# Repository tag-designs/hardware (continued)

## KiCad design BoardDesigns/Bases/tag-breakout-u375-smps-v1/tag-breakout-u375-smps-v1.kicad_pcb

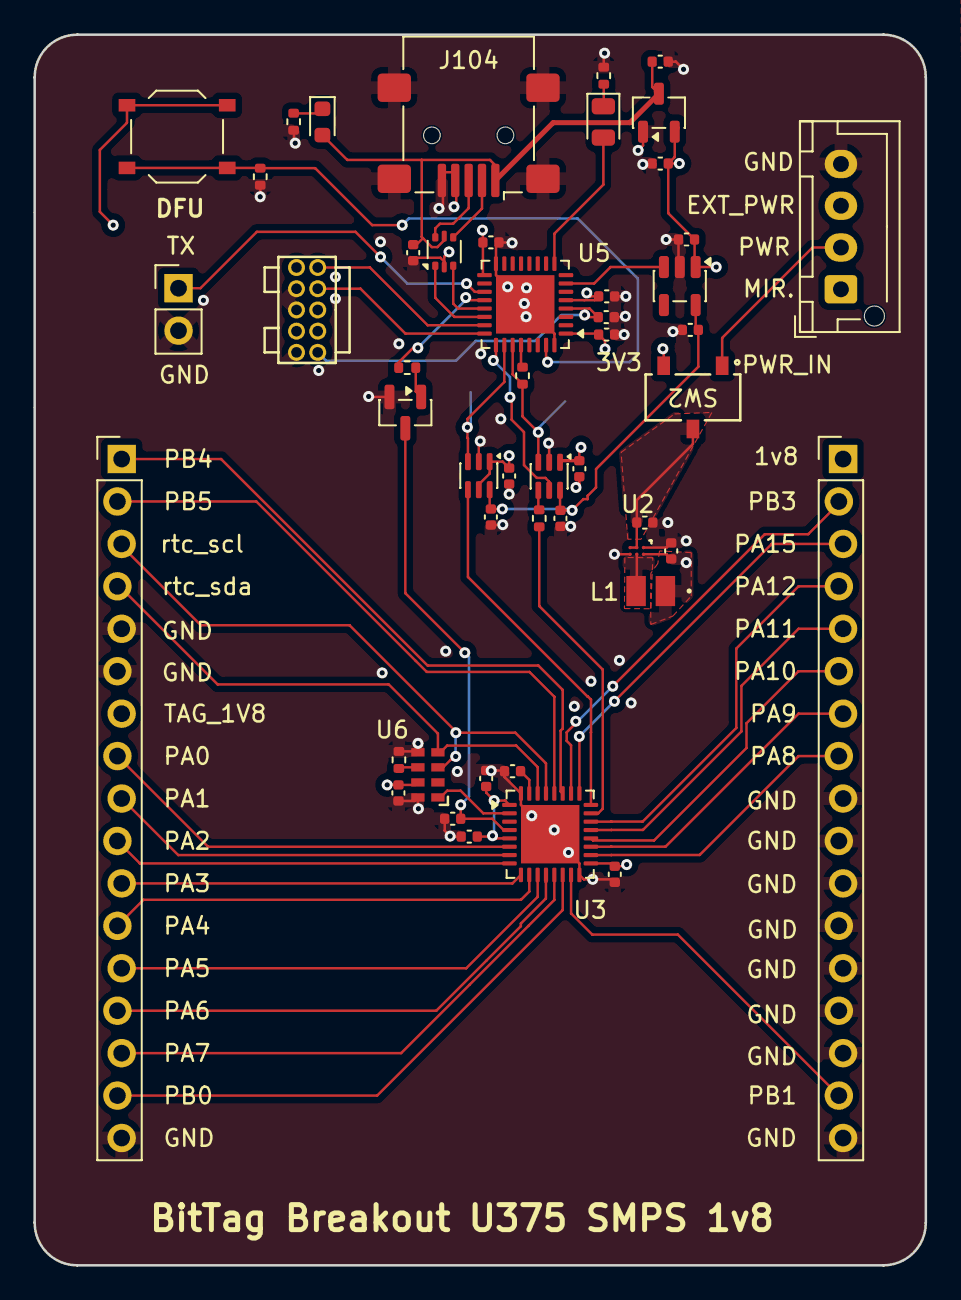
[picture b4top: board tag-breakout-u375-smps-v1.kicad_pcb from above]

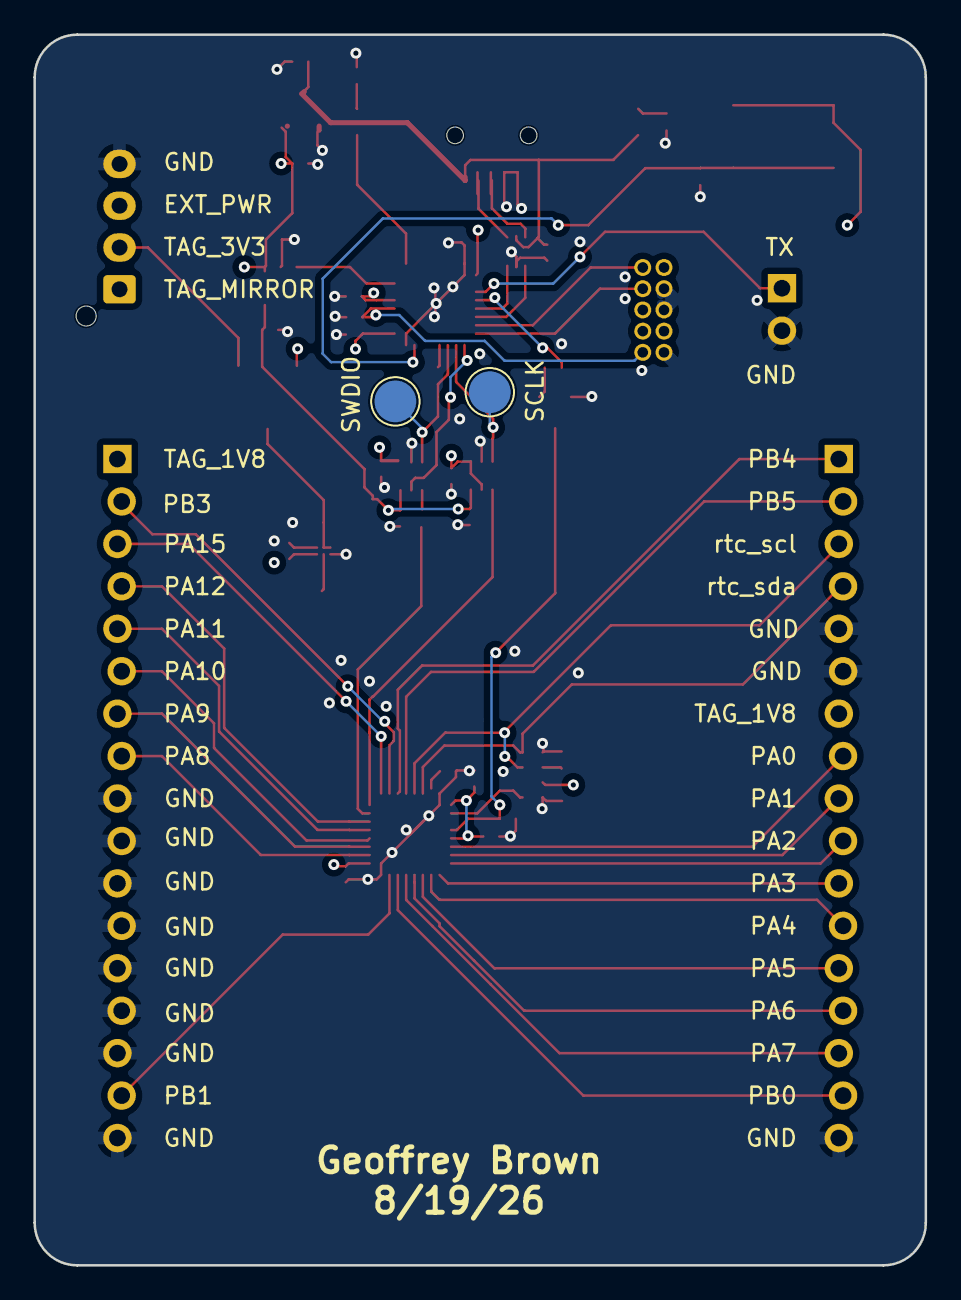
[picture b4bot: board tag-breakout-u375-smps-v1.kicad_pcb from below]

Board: 4 copper layers, 53.3 x 73.7 mm, 51 parts (2 on the bottom side), 55 nets.

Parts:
C1, C12, C104, C105: 1uF; C_0402_1005Metric
C2, C3, C5, C6, C7, C9, C11, C101, C102, C103, C107, C109, C110, C111: 0.1uF; C_0402_1005Metric
C4: 10uf; C_0402_1005Metric
C8, C10: 4.7uf; C_0402_1005Metric
D1: LED; LED_0805_2012Metric
D105: LED; LED_0603_1608Metric
J1: Conn_01x04_Female; JST_XH_B04B-XH-AM_1x04_P2.50mm_Vertical
J2: Conn_01x02_Male; PinHeader_1x02_P2.54mm_Vertical
J3, J4: Conn_01x17; PinHeader_1x17_P2.54mm_Vertical_Staggered
J102: Conn_02x05_Odd_Even; FTSH-105-01-F-D-K
J104: USB_B_Mini; USB_Mini-B_Lumberg_2486_01_Horizontal
L1: 2.2uH; IND_DFE2016_MUR
Q1: Q_NPN_BEC; SOT-23
R1, R2, R106: 100; R_0402_1005Metric
R3, R105: 12K; R_0402_1005Metric
R104: 2.2K; R_0402_1005Metric
R107: 200; R_0402_1005Metric
SW2: SW_SPDT; CJS-1200B_NDC
TP1, TP2: TestPoint; TestPoint_Pad_D2.5mm
U1: XC6206; SOT-23-3
U2: TPS62840YBGR; DSBGA6_1P4XP9_TEX
U3: stm32U375; UFQFPN-32-1EP_5x5mm_P0.5mm_EP3.5x3.5mm
U4: USBLC6-2P6; SOT-666
U5: STM32L432KBU6; UFQFPN-32-1EP_5x5mm_P0.5mm_EP3.5x3.5mm
U6: RV-3028-C7; RV-8803-C7
U7, U8: SN74LVC1T45DCK; SOT-363_SC-70-6
U10: AP2112K-1.8; SOT-23-5
U105: Tactile Switch; SW_SPST_TS_1187

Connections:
+1V8: C103.1, C105.1, C109.1, U7.6 (VCCB), U8.6 (VCCB), U10.5 (VOUT)
+3V3: C2.1, C11.1, C12.1, C104.1, C107.1, C110.1, C111.1, J102.1, SW2.3 (C), U1.2 (VO), U5.1 (VDD), U5.5 (VDDA/VREF+), U5.17 (VDD), U7.1 (VCCA), U7.5 (DIR), U8.1 (VCCA), U10.1 (VIN), U105.2 (B)
/DM: J104.2 (D-), U4.4 (I/O2)
/DP: J104.3 (D+), U4.6 (I/O1)
/LED_GREEN: D1.2 (A), U5.9 (PA3)
/NRST: C101.1, J102.10, U5.4 (~NRST)
/SCLK: J102.4, U5.24 (PA14)
/SWDIO: J102.2, U5.23 (PA13)
/UART_TX: J2.1, U5.19 (PA9)
/USB_DM: U4.3 (I/O2), U5.21 (PA11)
/USB_DP: U4.1 (I/O1), U5.22 (PA12)
/boot0: R105.2, U5.31 (BOOT0), U105.1 (A)
/en1.8v: U5.7 (PA1), U10.3 (EN)
/stm32/NRST: C5.1, Q1.3 (C), U3.4 (~NRST)
/stm32/PA0: J3.8, U3.6 (PA0)
/stm32/PA1: J3.9, U3.7 (PA1)
/stm32/PA2: J3.10, U3.8 (PA2)
/stm32/PA3: J3.11, U3.9 (PA3)
/stm32/PA4: J3.12, U3.10 (PA4)
/stm32/PA5: J3.13, U3.11 (PA5)
/stm32/PA6: J3.14, U3.12 (PA6)
/stm32/PA7: J3.15, U3.13 (PA7)
/stm32/PA8: J4.8, U3.18 (PA8)
/stm32/PA9: J4.7, U3.19 (PA9)
/stm32/PA10: J4.6, U3.20 (PA10)
/stm32/PA11: J4.5, U3.21 (PA11)
/stm32/PA12: J4.4, U3.22 (PA12)
/stm32/PA15: J4.3, U3.25 (PA15)
/stm32/PB0: J3.16, U3.14 (PB0)
/stm32/PB1: J4.16, U3.15 (PB1)
/stm32/PB3: J4.2, U3.26 (PB3)
/stm32/PB4: J3.1, U3.27 (PB4)
/stm32/PB5: J3.2, U3.28 (PB5)
/stm32/VBACK: R3.2, U6.6 (VBACK)
/stm32/clkout: U3.2 (PC14), U6.1 (CLKOUT)
/stm32/rtc_scl: J3.3, U3.29 (PB6), U6.3 (SCL)
/stm32/rtc_sda: J3.4, U3.30 (BOOT0-PB7), U6.4 (SDA)
GND: C1.2, C2.2, C3.2, C4.2, C5.2, C6.2, C7.2, C8.2, C9.2, C10.2, C11.2, C12.2, C101.2, C102.2, C103.2, C104.2, C105.2, C107.2, C109.2, C110.2, C111.2, J1.4, J2.2, J3.5, J3.6, J3.17, J4.9, J4.10, J4.11, J4.12, J4.13, J4.14, J4.15, J4.17, J102.3, J102.5, J102.9, J104.4 (ID), J104.5 (GND), J104.SH (Shield), Q1.2 (E), R1.2, R3.1, R105.1, R107.2, U1.1 (GND), U2.A1 (GND), U2.C2 (VSET), U3.16 (VSS), U3.32 (VSS), U3.33 (GND), U4.2 (GND), U5.16 (VSS), U5.32 (VSS), U5.33 (GND), U6.5 (GND), U6.8 (EVI), U7.2 (GND), U8.2 (GND), U10.2 (GND)
unnamed: D1.1 (K), R1.1
unnamed: D105.1 (K), R107.1
unnamed: L1.2, U2.B2 (SW)
unnamed: C8.1, U3.31 (VCAP)
unnamed: R104.1, U5.20 (PA10)
unnamed: U5.25 (PA15), U8.5 (DIR)
unnamed: TP2.1 (1_1), U5.26 (PB3), U7.3 (A)
unnamed: R2.2, TP1.1 (1_1), U5.27 (PB4), U8.3 (A)
unnamed: R2.1, U5.28 (PB5)
unnamed: R106.1, U8.4 (B)
PWR_IN: J1.2, SW2.1 (A)
TAG_1V8: C3.1, C4.1, C6.1, C7.1, C9.1, J3.7, J4.1, L1.1, U2.A2 (VOS), U3.1 (VDD), U3.5 (VDDA/VREF+), U3.17 (VDD), U6.7 (VDD)
TAG_3V3: C10.1, SW2.2 (B), U2.B1 (VIN), U2.C1 (EN)
TAG_RESET: Q1.1 (B), R104.2
TAG_SCK: U3.24 (PA14), U7.4 (B)
TAG_SWDIO: R106.2, U3.23 (PA13)
VUSB: C1.1, C102.1, D105.2 (A), J104.1 (VBUS), U1.3 (VI), U4.5 (VBUS)

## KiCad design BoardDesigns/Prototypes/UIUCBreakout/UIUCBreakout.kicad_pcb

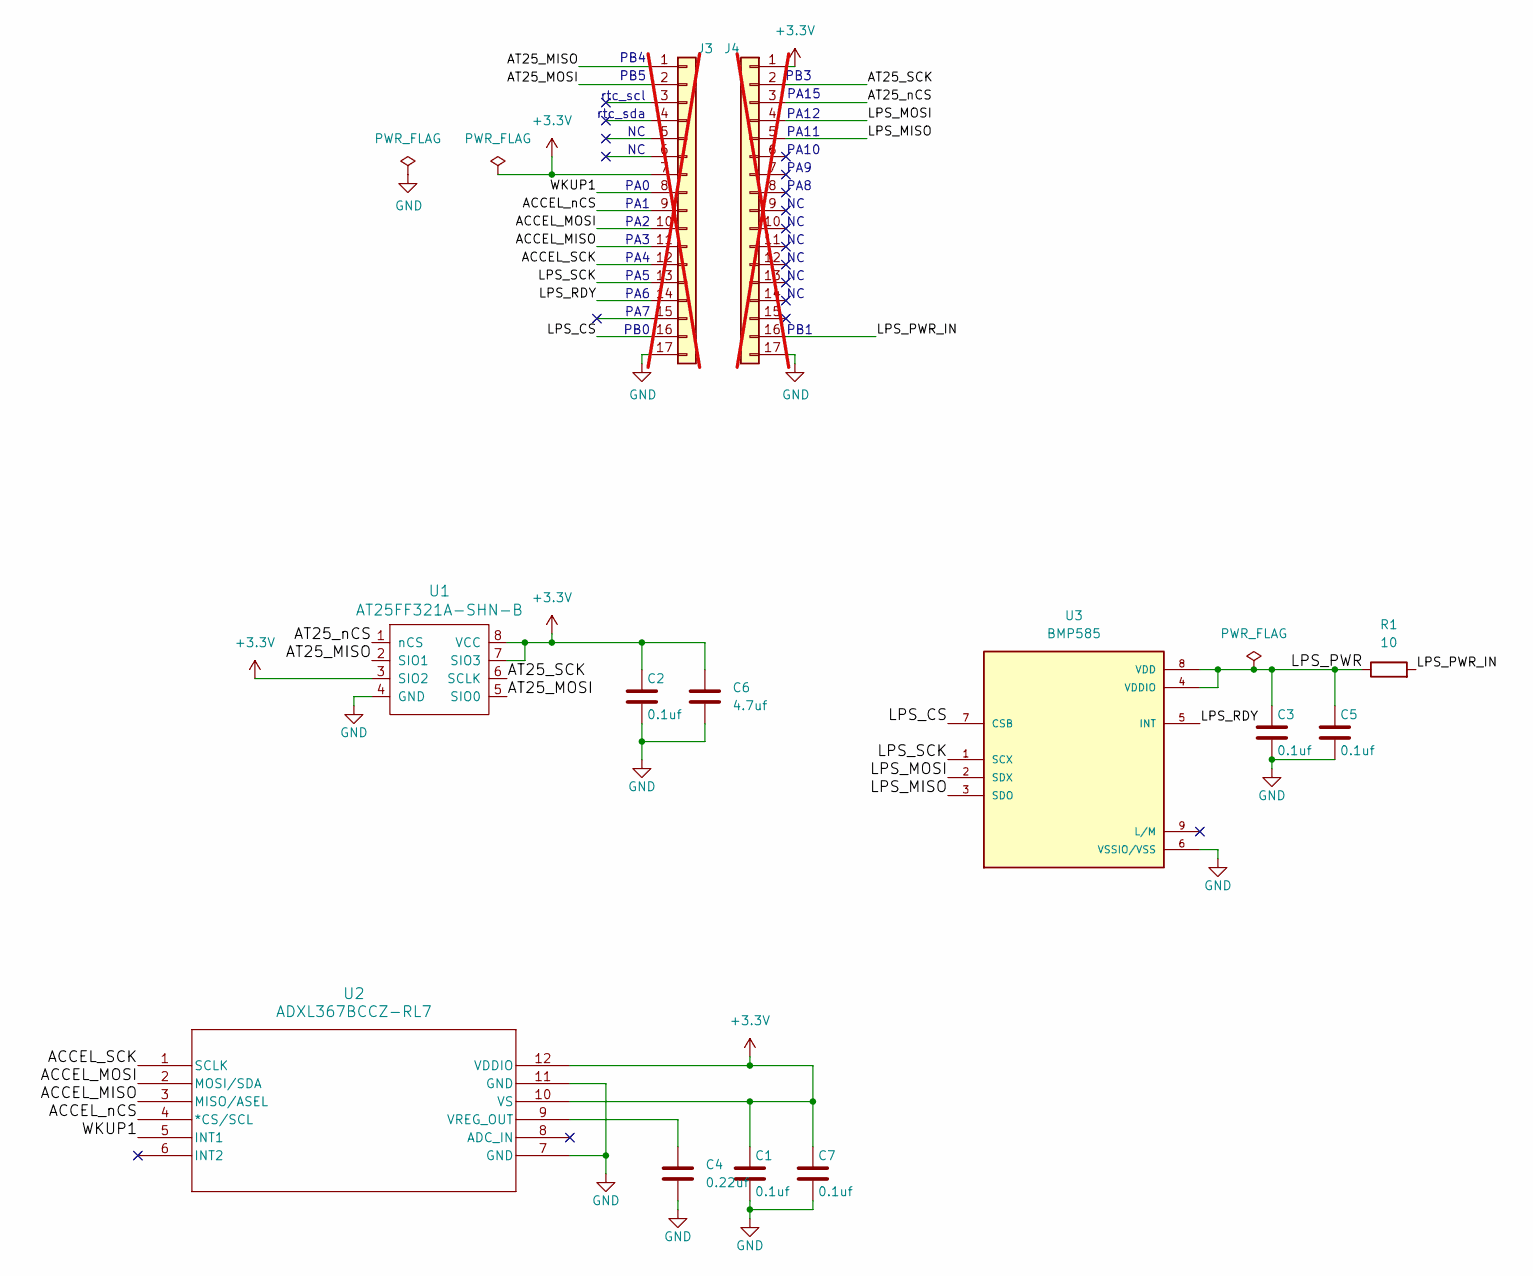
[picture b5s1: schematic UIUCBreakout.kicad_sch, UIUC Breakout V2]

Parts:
C1, C2, C3, C5, C7: 0.1uf; C_0603_1608Metric; MPN CC0603KRX7R9BB104; LCSC C14663
C4: 0.22uf; C_0603_1608Metric; MPN CL10B224KA8NNNC; LCSC C21120
C6: 4.7uf; C_0603_1608Metric; MPN CL10A475KO8NNNC; LCSC C19666
J3, J4: Conn_01x17; PinHeader_1x17_P2.54mm_Vertical_Staggered; not fitted
R1: 10; R_0603_1608Metric; MPN 0603WAF100JT5E; LCSC C22859
U1: AT25FF321A-SHN-B; SOIC-8_5.3x6.2mm_P1.27mm; MPN AT25FF321A-SHN-B; LCSC C5591126
U2: ADXL367BCCZ-RL7; CC-12-4_ADI; MPN ADXL367BCCZ-RL7; LCSC C17643415
U3: BMP585; LGA9_BMP585_BOS; PARTREV 1.2; LCSC C18184976

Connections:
+3.3V: C1.1, C2.1, C6.1, C7.1, J3.7, J4.1, U1.3 (SIO2), U1.7 (SIO3), U1.8 (VCC), U2.10 (VS), U2.12 (VDDIO)
/ACCEL_MISO: J3.11, U2.3 (MISO/ASEL)
/ACCEL_MOSI: J3.10, U2.2 (MOSI/SDA)
/ACCEL_SCK: J3.12, U2.1 (SCLK)
/ACCEL_nCS: J3.9, U2.4 (*CS/SCL)
/AT25_MISO: J3.1, U1.2 (SIO1)
/AT25_MOSI: J3.2, U1.5 (SIO0)
/AT25_SCK: J4.2, U1.6 (SCLK)
/AT25_nCS: J4.3, U1.1 (nCS)
/LPS_CS: J3.16, U3.7 (CSB)
/LPS_MISO: J4.5, U3.3 (SDO)
/LPS_MOSI: J4.4, U3.2 (SDX)
/LPS_PWR: C3.1, C5.1, R1.1, U3.4 (VDDIO), U3.8 (VDD)
/LPS_PWR_IN: J4.16, R1.2
/LPS_RDY: J3.14, U3.5 (INT)
/LPS_SCK: J3.13, U3.1 (SCX)
/WKUP1: J3.8, U2.5 (INT1)
GND: C1.2, C2.2, C3.2, C4.2, C5.2, C6.2, C7.2, J3.17, J4.17, U1.4 (GND), U2.7 (GND), U2.11 (GND), U3.6 (VSSIO/VSS)
unnamed: C4.1, U2.9 (VREG_OUT)

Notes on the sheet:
PA1
PA9
PA2
PA0
PA8
PA7
PA15
PA5
PA4
PB3
PA6
PA3
PB4
PA12
PB0
PB5
PA10
rtc_sda
PA11
PB1
rtc_scl

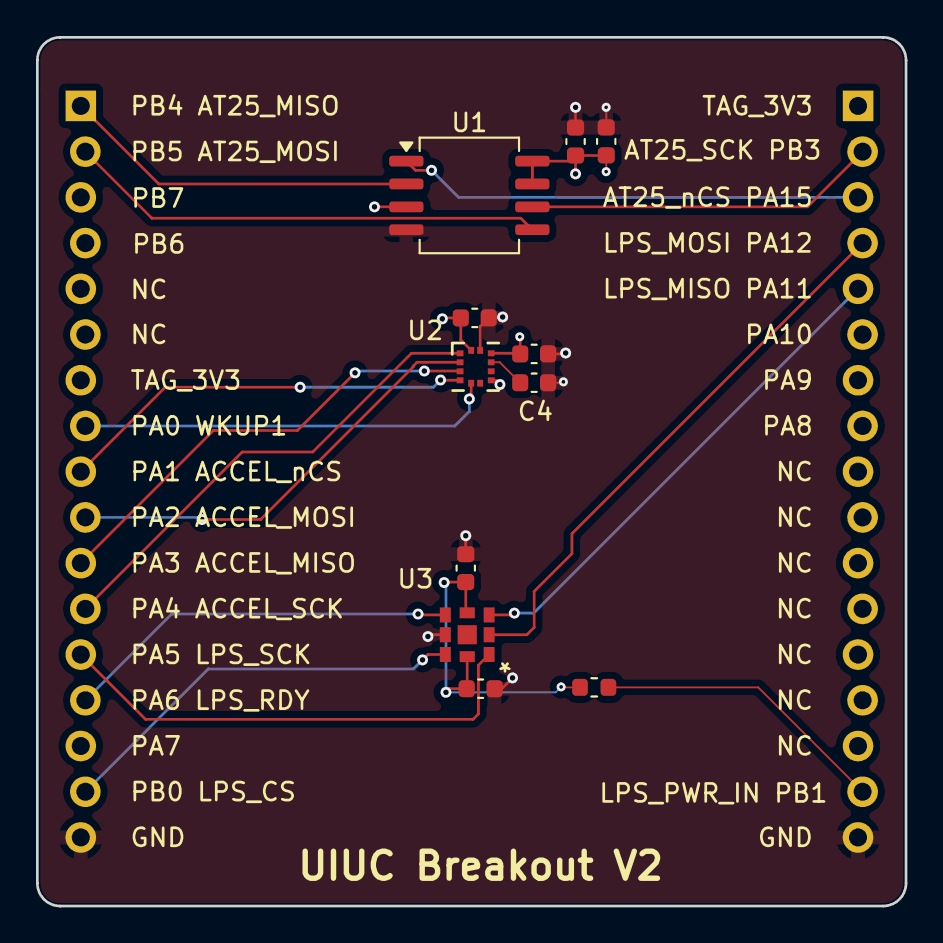
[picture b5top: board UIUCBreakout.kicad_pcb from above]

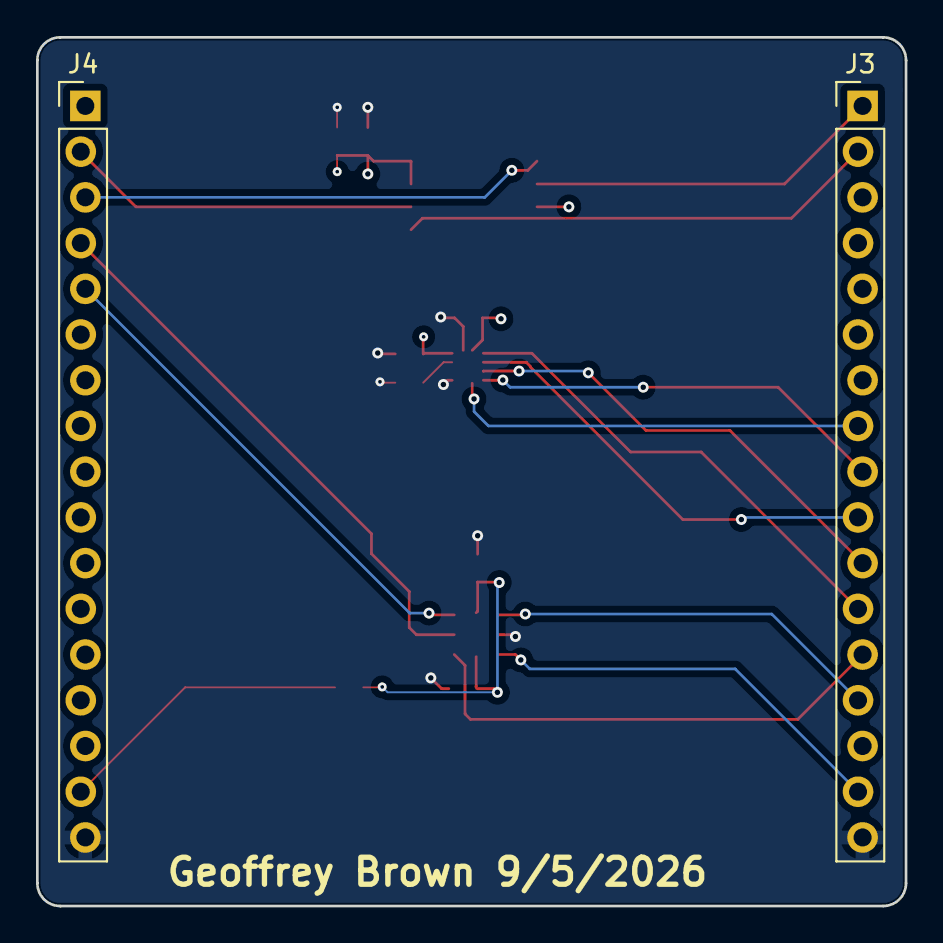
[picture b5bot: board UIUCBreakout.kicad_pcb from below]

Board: 4 copper layers, 48.3 x 48.3 mm, 13 parts (2 on the bottom side), 19 nets.

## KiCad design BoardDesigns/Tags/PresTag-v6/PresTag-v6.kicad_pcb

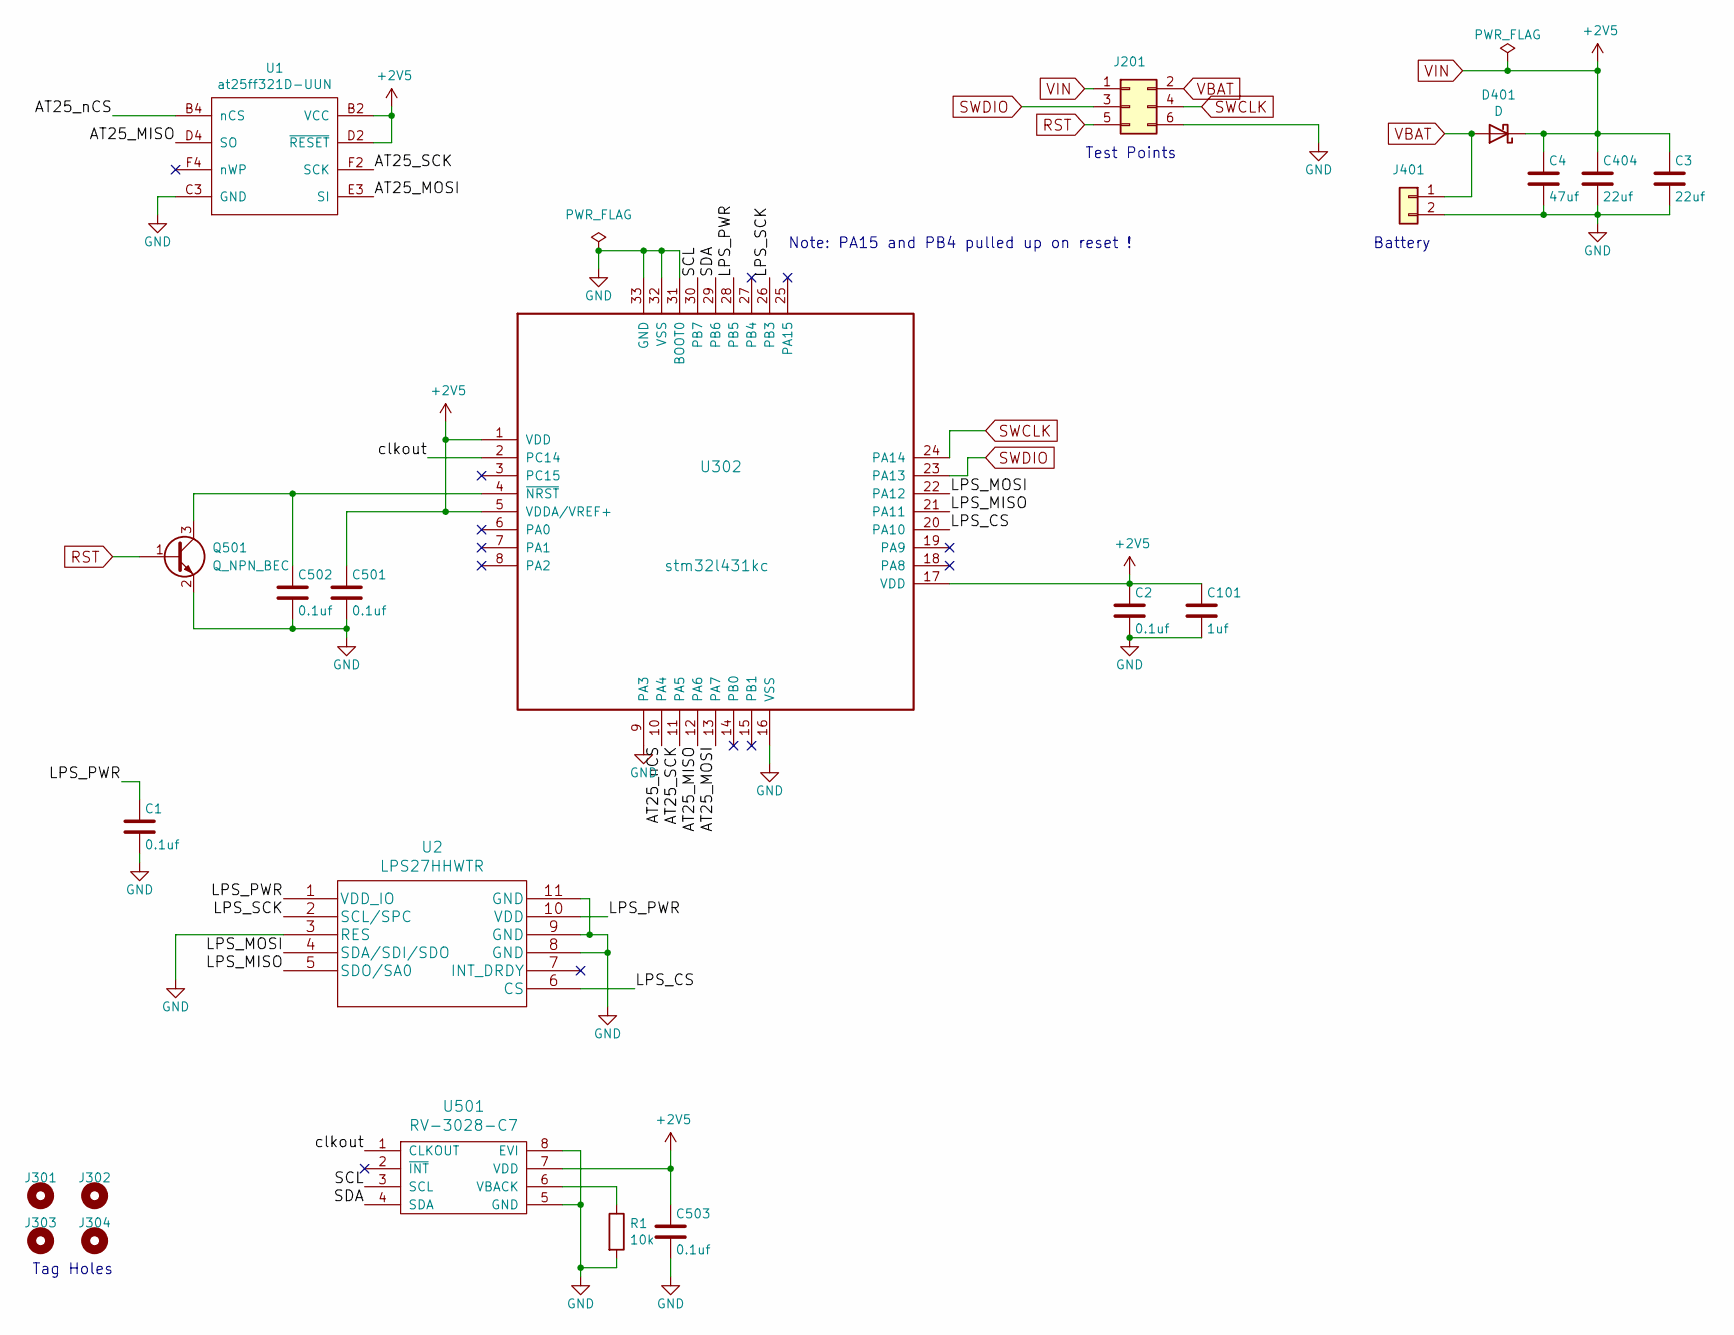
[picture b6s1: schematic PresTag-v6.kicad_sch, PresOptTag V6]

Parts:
C1, C2, C501, C502, C503: 0.1uf; C_0201_0603Metric; MPN GRM033C81E104KE14D
C3, C404: 22uf; C_0402_1005Metric; MPN 04026D226MAT2A
C4: 47uf; C_0603_1608Metric; MPN 06036D476MAT2A
C101: 1uf; C_0201_0603Metric; MPN GRM033R60J105MEA2D
D401: D; D_0402_1005Metric; MPN CDBQC0130L-HF
J201: CONN_02X04; tagpoints6
J301, J302, J303, J304: Conn_01x01; taghole1.1mm
J401: CONN_01X02; MS621
Q501: Q_NPN_BEC; SOT-883; MPN BC847AMB,315
R1: 10k; R_0201_0603Metric; MPN RC0201FR-0710KL
U1: at25ff321D-UUN; adesto_wlcsp12; MPN AT25FF321A-UUN-T (Mouser)
U2: LPS27HHWTR; MPN LPS27HHTWTR
U302: stm32l431kc; QFN-32-1EP_5x5mm_P0.5mm_EP3.45x3.45mm; MPN STM32L431KCU6
U501: RV-3028-C7; RV-8803-C7; MPN RV-3028-C7 32.768KHZ 1PPM-TA-QC

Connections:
/AT25_MISO: U1.D4 (SO), U302.12 (PA6)
/AT25_MOSI: U1.E3 (SI), U302.13 (PA7)
/AT25_SCK: U1.F2 (SCK), U302.11 (PA5)
/AT25_nCS: U1.B4 (nCS), U302.10 (PA4)
/LPS_CS: U2.6 (CS), U302.20 (PA10)
/LPS_MISO: U2.5 (SDO/SA0), U302.21 (PA11)
/LPS_MOSI: U2.4 (SDA/SDI/SDO), U302.22 (PA12)
/LPS_PWR: C1.1, U2.1 (VDD_IO), U2.10 (VDD), U302.28 (PB5)
/LPS_SCK: U2.2 (SCL/SPC), U302.26 (PB3)
/SCL: U302.30 (PB7), U501.3 (SCL)
/SDA: U302.29 (PB6), U501.4 (SDA)
/clkout: U302.2 (PC14), U501.1 (CLKOUT)
GND: C1.2, C2.2, C3.2, C4.2, C101.2, C404.2, C501.2, C502.2, C503.2, J201.6, J401.2, Q501.2 (E), R1.2, U1.C3 (GND), U2.3 (RES), U2.8 (GND), U2.9 (GND), U2.11 (GND), U302.9 (PA3), U302.16 (VSS), U302.31 (BOOT0), U302.32 (VSS), U302.33 (GND), U501.5 (GND), U501.8 (EVI)
unnamed: C502.1, Q501.3 (C), U302.4 (~NRST)
unnamed: R1.1, U501.6 (VBACK)
RST: J201.5, Q501.1 (B)
SWCLK: J201.4, U302.24 (PA14)
SWDIO: J201.3, U302.23 (PA13)
VBAT: D401.2 (A), J201.2, J401.1
VIN: C2.1, C3.1, C4.1, C101.1, C404.1, C501.1, C503.1, D401.1 (K), J201.1, U1.B2 (VCC), U1.D2 (~RESET), U302.1 (VDD), U302.5 (VDDA/VREF+), U302.17 (VDD), U501.7 (VDD)

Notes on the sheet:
Battery
Note: PA15 and PB4 pulled up on reset !
Tag Holes
Test Points

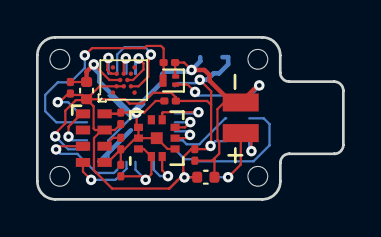
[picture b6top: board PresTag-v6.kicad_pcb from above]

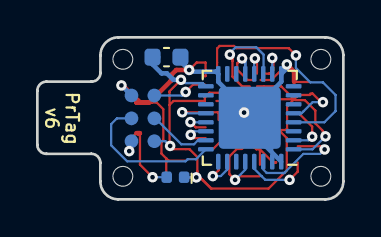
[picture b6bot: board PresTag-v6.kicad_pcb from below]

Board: 2 copper layers, 17.0 x 9.0 mm, 22 parts (4 on the bottom side), 20 nets.

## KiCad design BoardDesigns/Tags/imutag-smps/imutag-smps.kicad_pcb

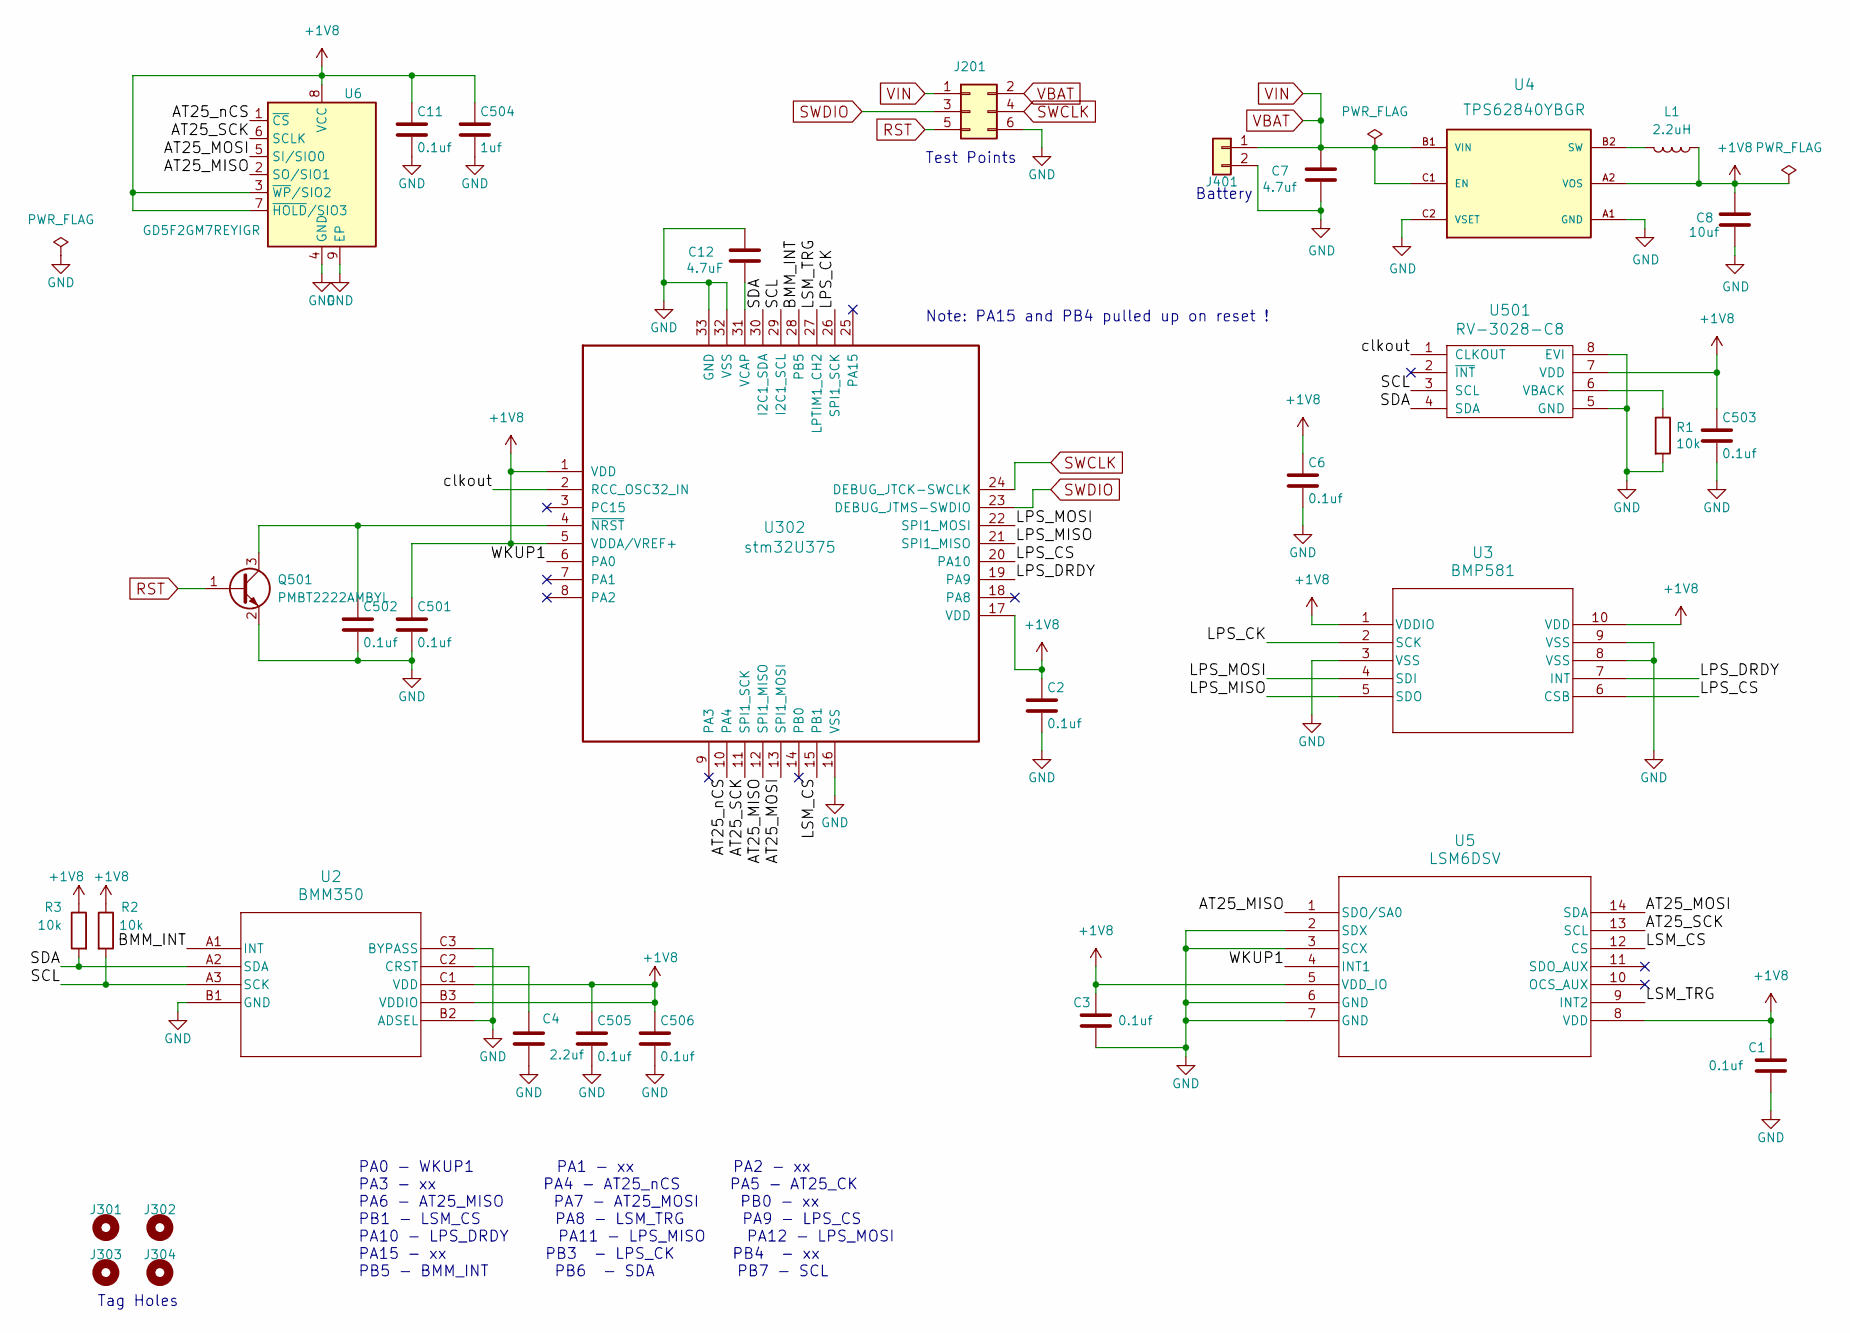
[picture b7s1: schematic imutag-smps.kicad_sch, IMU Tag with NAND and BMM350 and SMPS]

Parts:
C1, C2, C3, C6, C11, C501, C502, C503, C505, C506: 0.1uf; C_0201_0603Metric; MPN GRM033C81E104KE14D; LCSC C181047
C4: 2.2uf; C_0402_1005Metric; MPN GRM155R6YA225KE11D; LCSC C237392
C7: 4.7uf; C_0402_1005Metric; MPN GRM155R61A475MEAAD; LCSC C335105
C8: 10uf; C_0402_1005Metric; MPN GRM155R60J106ME15D; LCSC C412251
C12: 4.7uF; C_0402_1005Metric; MPN CL05A475MP5NRNC; LCSC C23733
C504: 1uf; C_0201_0603Metric; MPN GRM033R60J105MEA2D; LCSC C76930
J201: CONN_02X04; tagpoints6
J301, J302, J303, J304: Conn_01x01; taghole1.1mm
J401: CONN_01X02; batterypads
L1: 2.2uH; IND_DFE2016_MUR; MPN DFE201612E-2R2M=P2; LCSC C337893
Q501: PMBT2222AMBYL; SOT-883; MPN PMBT2222AMBYL; LCSC C552701
R1, R2, R3: 10k; R_0201_0603Metric; MPN RC0201FR-0710KL; LCSC C106225
U2: BMM350; BGA9_BMM350_BOS; MPN BMM350; LCSC C17225907
U3: BMP581; QFN10_BMP581_BOS; MPN BMP581; LCSC C5362283
U4: TPS62840YBGR; DSBGA6_1P4XP9_TEX; MPN TPS62840YBGR; LCSC C2071139
U5: LSM6DSV; LGA14-L_2P59X3P1X0P5_STM; MPN LSM6DSV; LCSC C5267399
U6: GD5F2GM7REYIGR; WSON-8-1EP_8x6mm_P1.27mm_EP3.4x4.3mm; MPN GD5F2GM7REYIGR; LCSC C23706308
U302: stm32U375; UFQFPN-32-1EP_5x5mm_P0.5mm_EP3.5x3.5mm; MPN STM32U375KGU6; LCSC C45338536
U501: RV-3028-C8; MPN RV-3028-C8-32.768kHz-1PPM-TA-QC; LCSC C46471039

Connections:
+1V8: C1.1, C2.1, C3.1, C6.1, C8.1, C11.1, C501.1, C503.1, C504.1, C505.1, C506.1, L1.1, R2.1, R3.1, U2.B3 (VDDIO), U2.C1 (VDD), U3.1 (VDDIO), U3.10 (VDD), U4.A2 (VOS), U5.5 (VDD_IO), U5.8 (VDD), U6.3 (~WP/SIO2), U6.7 (~HOLD/SIO3), U6.8 (VCC), U302.1 (VDD), U302.5 (VDDA/VREF+), U302.17 (VDD), U501.7 (VDD)
/AT25_MISO: U5.1 (SDO/SA0), U6.2 (SO/SIO1), U302.12 (SPI1_MISO)
/AT25_MOSI: U5.14 (SDA), U6.5 (SI/SIO0), U302.13 (SPI1_MOSI)
/AT25_SCK: U5.13 (SCL), U6.6 (SCLK), U302.11 (SPI1_SCK)
/AT25_nCS: U6.1 (~CS), U302.10 (PA4)
/BMM_INT: U2.A1 (INT), U302.28 (PB5)
/LPS_CK: U3.2 (SCK), U302.26 (SPI1_SCK)
/LPS_CS: U3.6 (CSB), U302.20 (PA10)
/LPS_DRDY: U3.7 (INT), U302.19 (PA9)
/LPS_MISO: U3.5 (SDO), U302.21 (SPI1_MISO)
/LPS_MOSI: U3.4 (SDI), U302.22 (SPI1_MOSI)
/LSM_CS: U5.12 (CS), U302.15 (PB1)
/LSM_TRG: U5.9 (INT2), U302.27 (LPTIM1_CH2)
/SCL: R2.2, U2.A3 (SCK), U302.29 (I2C1_SCL), U501.3 (SCL)
/SDA: R3.2, U2.A2 (SDA), U302.30 (I2C1_SDA), U501.4 (SDA)
/WKUP1: U5.4 (INT1), U302.6 (PA0)
/clkout: U302.2 (RCC_OSC32_IN), U501.1 (CLKOUT)
GND: C1.2, C2.2, C3.2, C4.2, C6.2, C7.2, C8.2, C11.2, C12.1, C501.2, C502.2, C503.2, C504.2, C505.2, C506.2, J201.6, J401.2, Q501.2 (E), R1.2, U2.B1 (GND), U2.B2 (ADSEL), U2.C3 (BYPASS), U3.3 (VSS), U3.8 (VSS), U3.9 (VSS), U4.A1 (GND), U4.C2 (VSET), U5.2 (SDX), U5.3 (SCX), U5.6 (GND), U5.7 (GND), U6.4 (GND), U6.9 (EP), U302.16 (VSS), U302.32 (VSS), U302.33 (GND), U501.5 (GND), U501.8 (EVI)
unnamed: C502.1, Q501.3 (C), U302.4 (~NRST)
unnamed: C4.1, U2.C2 (CRST)
unnamed: L1.2, U4.B2 (SW)
unnamed: C12.2, U302.31 (VCAP)
unnamed: R1.1, U501.6 (VBACK)
RST: J201.5, Q501.1 (B)
SWCLK: J201.4, U302.24 (DEBUG_JTCK-SWCLK)
SWDIO: J201.3, U302.23 (DEBUG_JTMS-SWDIO)
VBAT: C7.1, J201.1, J201.2, J401.1, U4.B1 (VIN), U4.C1 (EN)

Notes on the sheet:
Note: PA15 and PB4 pulled up on reset !
Tag Holes
Test Points
PA0 - WKUP1 PA1 - xx PA2 - xx PA3 - xx PA4 - AT25_nCS PA5 - AT25_CK PA6 - AT25_MISO PA7 - AT25_MOSI PB0 - xx PB1 - LSM_CS PA8 - LSM_TRG PA9 - LPS_CS PA10 - LPS_DRDY PA11 - LPS_MISO PA12 - LPS_MOSI PA15 - xx PB3 - LPS_CK PB4 - xx PB5 - BMM_INT PB6 - SDA PB7 - SCL
Battery

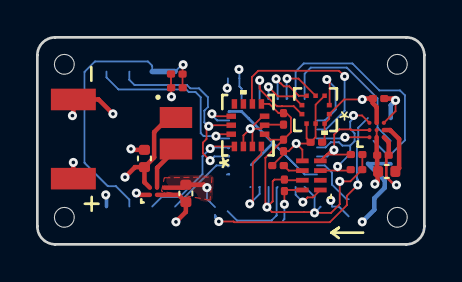
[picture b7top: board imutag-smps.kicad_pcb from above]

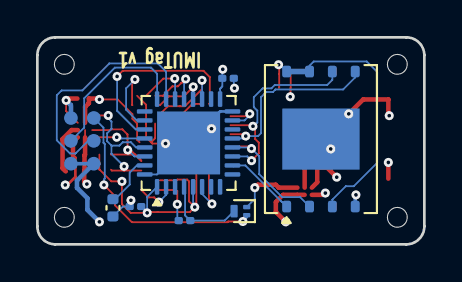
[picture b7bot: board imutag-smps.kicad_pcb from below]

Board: 4 copper layers, 21.5 x 11.5 mm, 33 parts (8 on the bottom side), 27 nets.

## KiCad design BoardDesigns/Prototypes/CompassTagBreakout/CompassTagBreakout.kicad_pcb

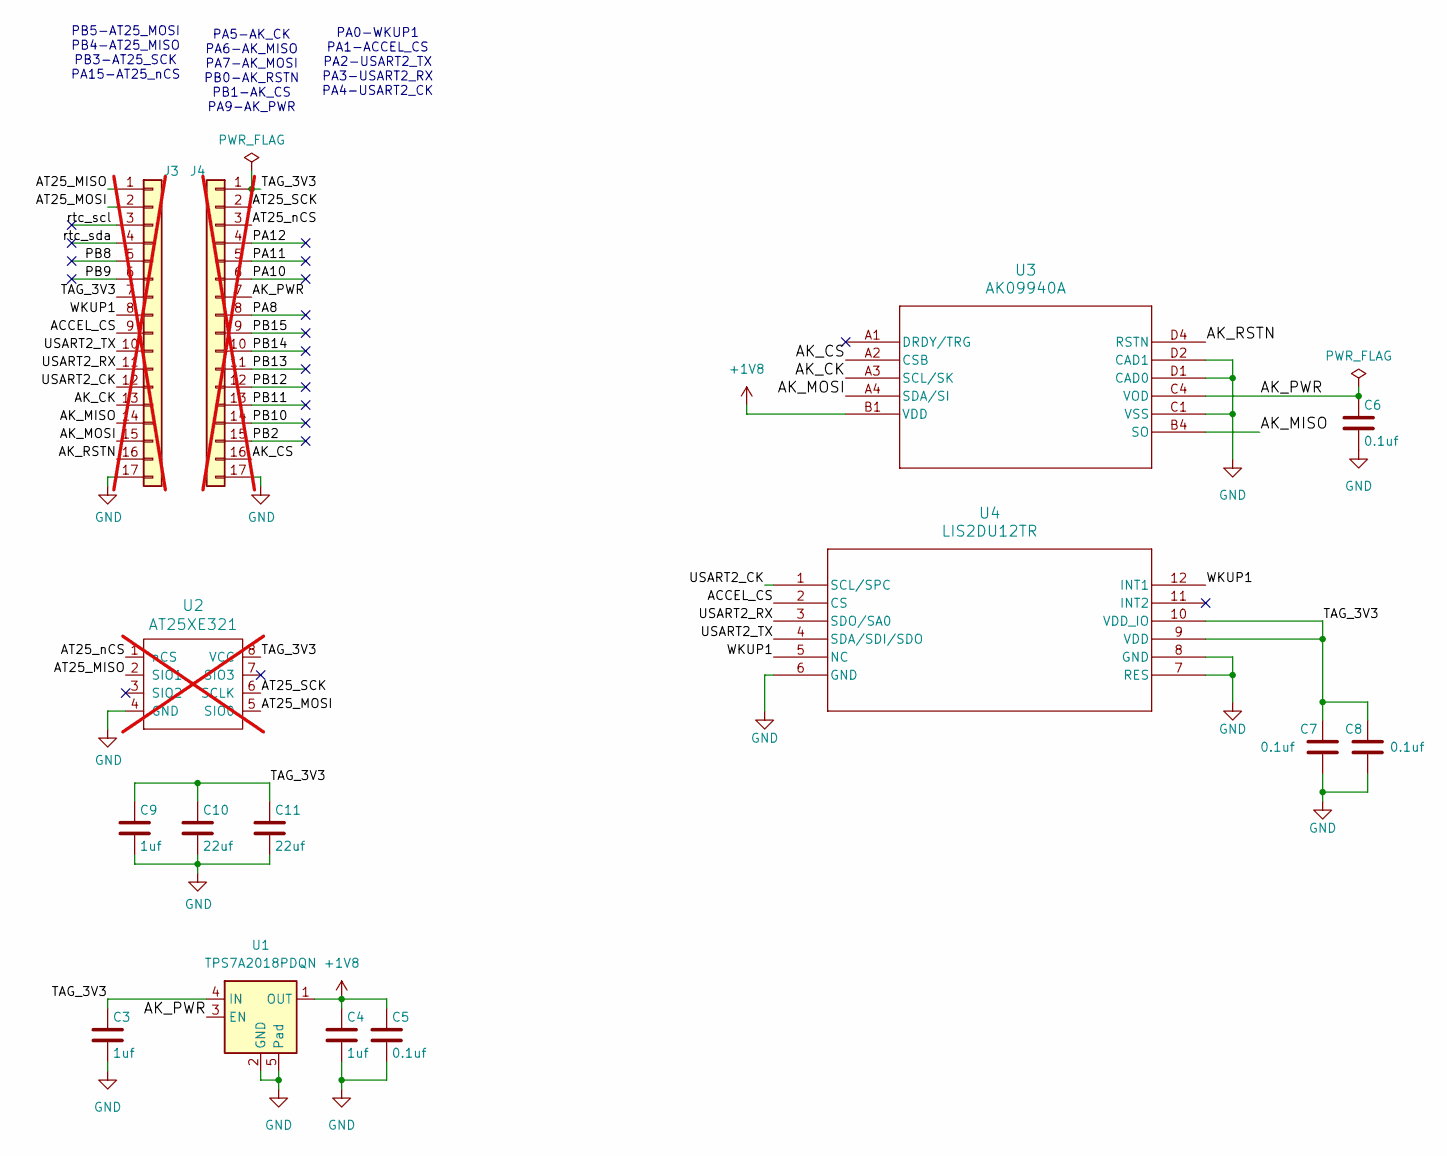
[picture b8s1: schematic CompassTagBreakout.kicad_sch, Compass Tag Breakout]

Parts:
C3, C4, C9: 1uf; C_0201_0603Metric; MPN GRM033R60J105MEA2D; LCSC C76930
C5, C6, C7, C8: 0.1uf; C_0201_0603Metric; MPN GRM033C81E104KE14D; LCSC C181047
C10, C11: 22uf; C_0402_1005Metric; MPN 04026D226MAT2A; LCSC C2179118
J3, J4: Conn_01x17; PinHeader_1x17_P2.54mm_Vertical_Staggered; not fitted
U1: TPS7A2018PDQN; Texas_X2SON-4_1x1mm_P0.65mm; MPN TPS7A2018PDQNR; LCSC C2878130
U2: AT25XE321; SO-8_5.3x6.2mm_P1.27mm; MPN AT25XE321D-SSHN-T; LCSC C7455379; not fitted
U3: AK09940A; AK09940a; MPN AK09940A; LCSC C6794828
U4: LIS2DU12TR; LGA-12L_LIS2DU12_STM; MPN LIS2DU12TR; LCSC C5267411

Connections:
+1V8: C4.1, C5.1, U1.1 (OUT), U3.B1 (VDD)
/ACCEL_CS: J3.9, U4.2 (CS)
/AK_CK: J3.13, U3.A3 (SCL/SK)
/AK_CS: J4.16, U3.A2 (CSB)
/AK_MISO: J3.14, U3.B4 (SO)
/AK_MOSI: J3.15, U3.A4 (SDA/SI)
/AK_PWR: C6.1, J4.7, U1.3 (EN), U3.C4 (VOD)
/AK_RSTN: J3.16, U3.D4 (RSTN)
/AT25_MISO: J3.1, U2.2 (SIO1)
/AT25_MOSI: J3.2, U2.5 (SIO0)
/AT25_SCK: J4.2, U2.6 (SCLK)
/AT25_nCS: J4.3, U2.1 (nCS)
/PA8: J4.8
/PA10: J4.6
/PA11: J4.5
/PA12: J4.4
/PB2: J4.15
/PB8: J3.5
/PB9: J3.6
/PB10: J4.14
/PB11: J4.13
/PB12: J4.12
/PB13: J4.11
/PB14: J4.10
/PB15: J4.9
/TAG_3V3: C3.1, C7.1, C8.1, C9.1, C10.1, C11.1, J3.7, J4.1, U1.4 (IN), U2.8 (VCC), U4.9 (VDD), U4.10 (VDD_IO)
/USART2_CK: J3.12, U4.1 (SCL/SPC)
/USART2_RX: J3.11, U4.3 (SDO/SA0)
/USART2_TX: J3.10, U4.4 (SDA/SDI/SDO)
/WKUP1: J3.8, U4.5 (NC), U4.12 (INT1)
/rtc_scl: J3.3
/rtc_sda: J3.4
GND: C3.2, C4.2, C5.2, C6.2, C7.2, C8.2, C9.2, C10.2, C11.2, J3.17, J4.17, U1.2 (GND), U1.5 (Pad), U2.4 (GND), U3.C1 (VSS), U3.D1 (CAD0), U3.D2 (CAD1), U4.6 (GND), U4.7 (RES), U4.8 (GND)

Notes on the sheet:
PA5-AK_CK PA6-AK_MISO PA7-AK_MOSI PB0-AK_RSTN PB1-AK_CS PA9-AK_PWR
PA0-WKUP1 PA1-ACCEL_CS PA2-USART2_TX PA3-USART2_RX PA4-USART2_CK
PB5-AT25_MOSI PB4-AT25_MISO PB3-AT25_SCK PA15-AT25_nCS

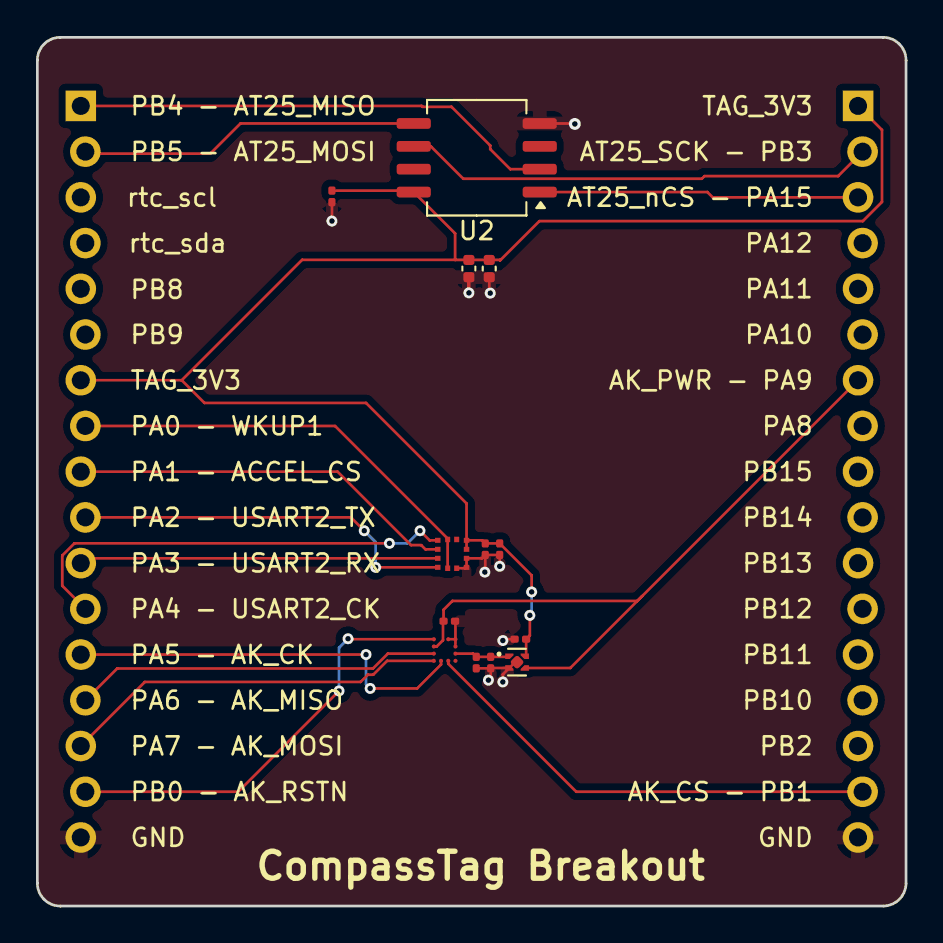
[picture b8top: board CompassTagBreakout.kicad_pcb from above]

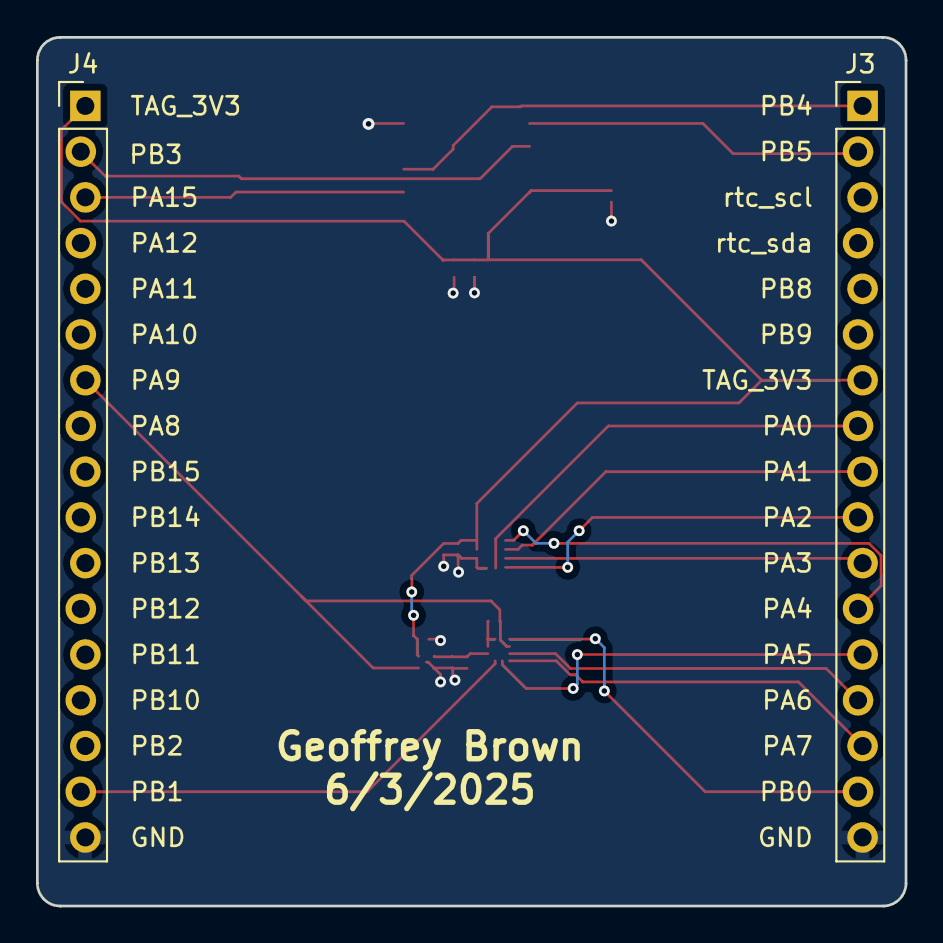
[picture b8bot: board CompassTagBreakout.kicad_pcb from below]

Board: 2 copper layers, 48.3 x 48.3 mm, 15 parts (2 on the bottom side), 18 nets.
